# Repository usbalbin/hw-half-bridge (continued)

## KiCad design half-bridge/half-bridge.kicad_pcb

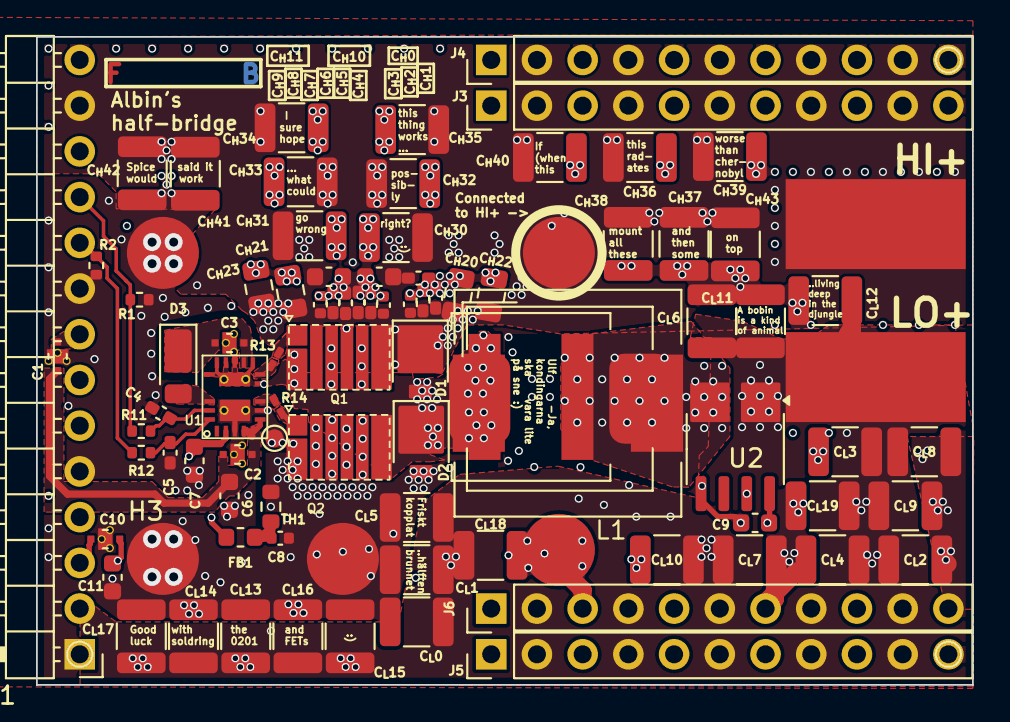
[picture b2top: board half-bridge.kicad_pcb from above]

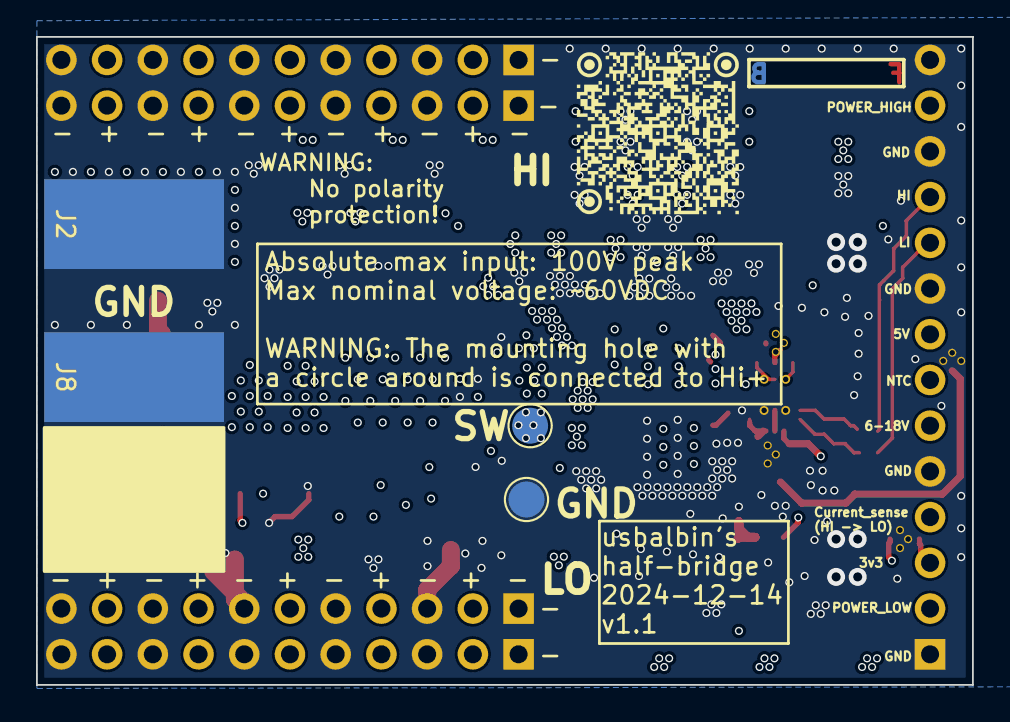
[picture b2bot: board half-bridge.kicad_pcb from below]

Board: 8 copper layers, 52.0 x 36.0 mm, 99 parts (4 on the bottom side), 23 nets.

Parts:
C1, C2, C3, C10: YFF18PW0J474M; C_0603_1608Metric_Feedthrough_W_0.45Vias
C4, C5: ?pF; C_0402_1005Metric_Pad0.74x0.62mm_HandSolder
C6, C7, C11: 10u; C_0603_1608Metric
C8: 100nF; C_0402_1005Metric
C9: 100nF; C_0603_1608Metric
C_{H}0, C_{H}1, C_{H}2, C_{H}5, C_{H}6, C_{H}7, C_{H}8: 100nF; C_0402_1005Metric_Pad0.74x0.62mm_HandSolder
C_{H}3, C_{H}4, C_{H}9: 100nF; C_0402_1005Metric
C_{H}10, C_{H}11: 220nF; C_0603_1608Metric
C_{H}20, C_{H}21, C_{H}22, C_{H}23: 1uF; C_0805_2012Metric
C_{H}30, C_{H}31, C_{H}32, C_{H}33, C_{H}34, C_{H}35, C_{H}36, C_{H}37, C_{H}38, C_{H}39, C_{H}40, C_{H}41, C_{H}42, C_{H}43: 10uF; C_1210_3225Metric
C_{L}0, C_{L}1, C_{L}2, C_{L}3, C_{L}4, C_{L}5, C_{L}6, C_{L}7, C_{L}8, C_{L}9, C_{L}10, C_{L}11, C_{L}12, C_{L}13, C_{L}14, C_{L}15, C_{L}16, C_{L}17, C_{L}18, C_{L}19: 10uF; C_1210_3225Metric
D1, D2: D_Schottky; D_SMP_DO-220AA
D3: DFLS1100; D_PowerDI-123
FB1: FerriteBead; L_0603_1608Metric
FID1, FID2, FID3: Fiducial; TestPoint_Pad_D1.0mm
H1, H2, H3, H4, H5: WE 97730256330; Mounting_Wuerth_WA-SMSI-M1.6_H2.5mm_ThreadDepth1.5mm_NoNPTH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
J1: Angled PinHeader 1x14; PinHeader_1x14_P2.54mm_Horizontal
J2, J7, J8, J9: Solder_Pad; SolderWirePad_1x01_SMD_5x10mm
J3, J4, J5, J6: PinSocket 1x11; PinHeader_1x11_P2.54mm_Vertical
L1: ind=1.76uH esr=9.77m epc=9.28pF; L_Coilcraft_XAL8080-XXX
L4: L_Wuerth_WE-PD-Typ-LS
L5: L_Bourns_SRP1050WA
Q1, Q2: EPC2306; EPC PQFN 3x5 mm
R1, R2: 15k; R_0402_1005Metric
R11, R12: 100R; R_0402_1005Metric
R13, R14: 1R; R_0201_0603Metric_Pad0.64x0.40mm_HandSolder
TH1: 10k; R_0603_1608Metric
TP1, TP2: TestPoint; TestPoint_Pad_D2.0mm
TP3: TestPoint; TestPoint_Pad_D1.0mm
U1: LMG1210; lmg1210
U2: ACS37030; ACS3703x

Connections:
0: C1.2, C2.2, C4.2, C5.2, C6.2, C7.2, C8.2, C9.1, C10.2, C11.2, C_{H}0.2, C_{H}1.2, C_{H}2.2, C_{H}3.2, C_{H}4.2, C_{H}5.2, C_{H}6.2, C_{H}7.2, C_{H}8.2, C_{H}9.2, C_{H}10.2, C_{H}11.2, C_{H}20.2, C_{H}21.2, C_{H}22.2, C_{H}23.2, C_{H}30.2, C_{H}31.2, C_{H}32.2, C_{H}33.2, C_{H}34.2, C_{H}35.2, C_{H}36.2, C_{H}37.2, C_{H}38.2, C_{H}39.2, C_{H}40.2, C_{H}41.2, C_{H}42.2, C_{H}43.2, C_{L}0.2, C_{L}1.2, C_{L}2.2, C_{L}3.2, C_{L}4.2, C_{L}5.2, C_{L}6.2, C_{L}7.2, C_{L}8.2, C_{L}9.2, C_{L}10.2, C_{L}11.2, C_{L}12.2, C_{L}13.2, C_{L}14.2, C_{L}15.2, C_{L}16.2, C_{L}17.2, C_{L}18.2, C_{L}19.2, D2.2 (A), H1.1, H3.1, H4.1, H5.1, J1.1, J1.5, J1.9, J1.12, J1.14, J2.1, J3.1, J3.3, J3.5, J3.7, J3.9, J3.11, J4.1, J4.3, J4.5, J4.7, J4.9, J4.11, J5.1, J5.3, J5.5, J5.7, J5.9, J5.11, J6.1, J6.3, J6.5, J6.7, J6.9, J6.11, J8.1, Q2.2 (S), Q2.4 (S), Q2.6 (S), R1.1, R2.1, TH1.2, TP2.1, TP3.1, U1.3 (Vss), U1.7 (Vss), U1.20 (Vss), U2.3 (GND)
6-18V: C7.1, J1.6, U1.2 (Vin)
+3V3: C9.2, C10.3, C11.1, U2.6 (VDD)
+5V: C1.3, C2.1, C2.3, C6.1, U1.4 (Vdd), U1.5 (DHL), U1.6 (DLH)
/HI: J1.11, R1.2, R11.1
/HO: R13.1, U1.10 (HO)
/I_Shunt: L1.2, L4.2, L5.2, U2.2 (IP-)
/LI: J1.10, R2.2, R12.1
/LO: R14.1, U1.8 (LO)
Current_sense: J1.4, U2.5 (VOUT)
Gate_hi: Q1.1 (G), R13.2
Gate_lo: Q2.1 (G), R14.2
NTC: FB1.1, J1.7
unnamed: C8.1, FB1.2, TH1.1
unnamed: D3.2 (A), U1.17 (BST)
unnamed: C3.1, C3.3, D3.1 (K), U1.12 (HB)
unnamed: C10.1, J1.3
unnamed: C1.1, J1.8
unnamed: C4.1, R11.2, U1.18 (EN/HI)
unnamed: C5.1, R12.2, U1.19 (PWM/LO)
POWER_HIGH: C_{H}0.1, C_{H}1.1, C_{H}2.1, C_{H}3.1, C_{H}4.1, C_{H}5.1, C_{H}6.1, C_{H}7.1, C_{H}8.1, C_{H}9.1, C_{H}10.1, C_{H}11.1, C_{H}20.1, C_{H}21.1, C_{H}22.1, C_{H}23.1, C_{H}30.1, C_{H}31.1, C_{H}32.1, C_{H}33.1, C_{H}34.1, C_{H}35.1, C_{H}36.1, C_{H}37.1, C_{H}38.1, C_{H}39.1, C_{H}40.1, C_{H}41.1, C_{H}42.1, C_{H}43.1, D1.1 (K), H2.1, J1.13, J3.2, J3.4, J3.6, J3.8, J3.10, J4.2, J4.4, J4.6, J4.8, J4.10, J7.1, Q1.3 (D), Q1.5 (D), Q1.7 (D)
POWER_LOW: C_{L}0.1, C_{L}1.1, C_{L}2.1, C_{L}3.1, C_{L}4.1, C_{L}5.1, C_{L}6.1, C_{L}7.1, C_{L}8.1, C_{L}9.1, C_{L}10.1, C_{L}11.1, C_{L}12.1, C_{L}13.1, C_{L}14.1, C_{L}15.1, C_{L}16.1, C_{L}17.1, C_{L}18.1, C_{L}19.1, J1.2, J5.2, J5.4, J5.6, J5.8, J5.10, J6.2, J6.4, J6.6, J6.8, J6.10, J9.1, U2.1 (IP+)
Switch_node: C3.2, D1.2 (A), D2.1 (K), L1.1, L4.1, L5.1, Q1.2 (S), Q1.4 (S), Q1.6 (S), Q2.3 (D), Q2.5 (D), Q2.7 (D), TP1.1, U1.9 (HS), U1.11 (HS), U1.13 (HS), U1.14 (HS), U1.15 (HS), U1.16 (HS), U1.21 (HS)

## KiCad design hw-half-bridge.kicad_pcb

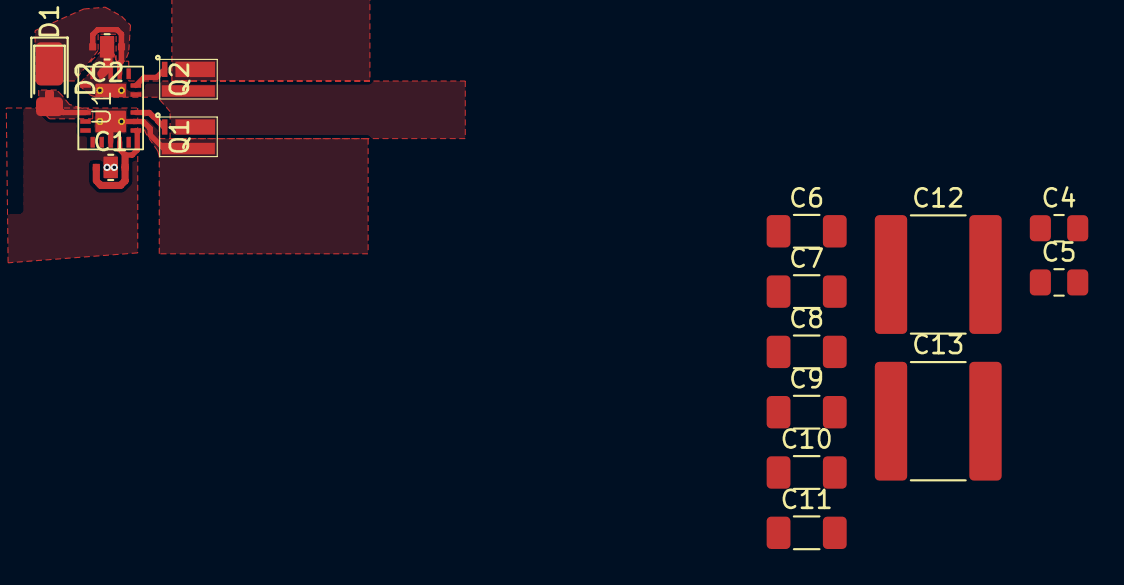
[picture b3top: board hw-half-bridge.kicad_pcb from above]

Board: 2 copper layers, 18 parts (0 on the bottom side), 9 nets.

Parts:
C1, C2: YFF18PW0J474M; C_0603_1608Metric_Feedthrough
C4, C5: C_Small; C_0805_2012Metric_Pad1.18x1.45mm_HandSolder
C6, C7, C8, C9, C10, C11: C; C_1206_3216Metric_Pad1.33x1.80mm_HandSolder
C12, C13: C; C_2225_5664Metric_Pad1.80x6.60mm_HandSolder
D1: BAT46; D_SOD-323F
D2: DFLS1200; D_PowerDI-123
NT1: NetTie-2_SMD_Pad0.5mm
Q1, Q2: GAN7R0-150LBE; FCLGA3(SOT8073-1)
U1: LMG1210; lmg1210

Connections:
5V: C1.1, C1.3, U1.4 (Vdd), U1.6 (DLH)
Earth: C1.2, NT1.1, U1.3 (Vss), U1.20 (Vss)
Gate_hi: Q2.1 (G), U1.10 (HO)
Gate_lo: Q1.1 (G), U1.8 (LO)
unnamed: D1.2 (A), D2.2 (A), U1.17 (BST)
unnamed: C2.1, C2.3, D1.1 (K), D2.1 (K), U1.12 (HB)
unnamed: C2.2, Q1.3 (D), Q2.2 (S), U1.9 (HS), U1.11 (HS), U1.13 (HS), U1.14 (HS), U1.15 (HS), U1.16 (HS), U1.21 (HS)
PGND: C4.2, C5.2, C6.2, C7.2, C8.2, C9.2, C10.2, C11.2, C12.2, C13.2, NT1.2, Q1.2 (S), U1.7 (Vss)
Vbus: C4.1, C5.1, C6.1, C7.1, C8.1, C9.1, C10.1, C11.1, C12.1, C13.1, Q2.3 (D)

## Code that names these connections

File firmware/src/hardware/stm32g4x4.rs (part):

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    delay::SYSTDelayExt,
    gpio::{
        self,
        gpioa::{PA0, PA1, PA2, PA3, PA4, PA5, PA6, PA7},
        gpiob::{PB0, PB11, PB14, PB2},
        gpioc::{PC0, PC1, PC2, PC3, PC4, PC5},
        gpiof::{PF0, PF1},
        GpioExt,
    },
    observable::{Observable, ObservationLock, ObservationToken, Observed},
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            usb_pd: stm32::UCPD1,

            #[allow(dead_code)]
            usb_dm: gpio::gpioa::PA11<gpio::Input<gpio::Floating>>,
            #[allow(dead_code)]
            usb_dp: gpio::gpioa::PA12<gpio::Input<gpio::Floating>>,

            #[allow(dead_code)]
            cc1: gpio::gpiob::PB6<gpio::Input<gpio::Floating>>,
            #[allow(dead_code)]
            cc2: gpio::gpiob::PB4<gpio::Input<gpio::Floating>>,

            #[allow(dead_code)]
            #[cfg(feature = "usb-pd-db")]
            dbcc1: gpio::gpioa::PA9<gpio::Input<gpio::Floating>>,

            #[allow(dead_code)]
            #[cfg(feature = "usb-pd-db")]
            dbcc2: gpio::gpioa::PA10<gpio::Input<gpio::Floating>>,

            frs: gpio::gpioc::PC12<gpio::Input<gpio::Floating>>,

            en_vconn: gpio::gpioc::PC10<gpio::Input<gpio::Floating>>,

            en_cc: gpio::gpioc::PC13<gpio::Input<gpio::Floating>>,

            // Used to select cc-line for usb pd cable orientation
            cc_select: gpio::gpioc::PC14<gpio::Input<gpio::Floating>>,

            // Use to select direction of current measurements 2-5
            cc_dir: gpio::gpioc::PC15<gpio::Input<gpio::Floating>>,
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
        struct Swd {
            #[allow(dead_code)]
            swdio: gpio::gpioa::PA13<gpio::Input<gpio::Floating>>,
            #[allow(dead_code)]
            swc: gpio::gpioa::PA14<gpio::Input<gpio::Floating>>,
        }

        let pa0 = gpioa.pa0;
        let pa1 = gpioa.pa1;
        let pa2 = gpioa.pa2;
        let pa3 = gpioa.pa3;
        let pa4 = gpioa.pa4;
        let pa5 = gpioa.pa5;
        let pa6 = gpioa.pa6;
        let pa7 = gpioa.pa7;
        let pa8 = gpioa.pa8;
        let pa9 = gpioa.pa9;
        let pa10 = gpioa.pa10;
        let pa11 = gpioa.pa11;
        let pa12 = gpioa.pa12;
        let pa13 = gpioa.pa13;
        let pa14 = gpioa.pa14;
        let pa15 = gpioa.pa15;

        let pb0 = gpiob.pb0;
        let pb1 = gpiob.pb1;
        let pb2 = gpiob.pb2;
        let pb3 = gpiob.pb3;
        let pb4 = gpiob.pb4;
        let pb5 = gpiob.pb5;
        let pb6 = gpiob.pb6;
        let pb7 = gpiob.pb7;
        let pb8 = gpiob.pb8;
        let pb9 = gpiob.pb9;
        let pb10 = gpiob.pb10;
        let pb11 = gpiob.pb11;
        let pb12 = gpiob.pb12;
        let pb13 = gpiob.pb13;
        let pb14 = gpiob.pb14;
        let pb15 = gpiob.pb15;

        let pc0 = gpioc.pc0;
        let pc1 = gpioc.pc1;
        let pc2 = gpioc.pc2;
        let pc3 = gpioc.pc3;
        let pc4 = gpioc.pc4;
        let pc5 = gpioc.pc5;
        let pc6 = gpioc.pc6;
        let pc7 = gpioc.pc7;
        let pc8 = gpioc.pc8;
        let pc9 = gpioc.pc9;
        let pc10 = gpioc.pc10;
        let pc11 = gpioc.pc11;
        let pc12 = gpioc.pc12;
        let pc13 = gpioc.pc13;
        let pc14 = gpioc.pc14;
        let pc15 = gpioc.pc15;

        let pd2 = gpiod.pd2;

        let pf0 = gpiof.pf0;
        let pf1 = gpiof.pf1;

        // LO: CC1 and CC2 are connected to PA9 and PA10
        // HI: HI_4, LI_4, HI_5 and LI_5 are connected to PA8,9,10 and PB15
        let cc_hi4_hi5_mux = pd2.into_push_pull_output();

        //let pg10 = gpiog.pg10;comp3_b_fb_d_cc1b_pin
        //let _reset_pin = pg10;
        let _boot_pin = pb8;

        let _swd = Swd {
            swdio: pa13,
            swc: pa14,
        };

        let _usb = FakeUsb {
            usb,
            usb_pd: usb_pd,

            usb_dm: pa11,
            usb_dp: pa12,

            cc1: pb6,
            cc2: pb4,

            #[cfg(feature = "usb-pd-db")]
            dbcc1: pa9,
            #[cfg(feature = "usb-pd-db")]
            dbcc2: pa10,

            frs: pc12,
            en_vconn: pc10,
            en_cc: pc13,

            cc_select: pc14,
            cc_dir: pc15,
        };

        // HRTIMF
        let hi_1 = pc6;
        let li_1 = pc7;

        // HRTIMC
        let hi_2 = pb12;
        let li_2 = pb13;

        // HRTIME
        let hi_3 = pc8;
        let li_3 = pc9;

        // HRTIMD
        #[cfg(feature = "hv4")]
        let li_4 = pb15; // HRTIMD

        #[cfg(feature = "hv4")]
        let hi_4 = pa10; // HRTIMB
                         //let li_b = pa11; // HRTIMB <--- Used by USB_DP

        // HRTIMA
        #[cfg(feature = "hv5")]
        let hi_5 = pa8;
        #[cfg(feature = "hv5")]
        let li_5 = pa9; // Used by dbcc1

        let pwm_led1 = pb5.into_alternate(); // 5v tol
        let pwm_led2 = pb7.into_alternate(); // 5v tol
        let pwm_led3 = pb9.into_alternate(); // 5v tol

        let pwm_led4 = pb10.into_alternate(); // 3.6v max
                                              //let pwm_led5 = pa3.into_alternate(); // 3.6v max
        let pwm_led6_pot3_adc1_in12_adc3_in1 = pb1.into_alternate(); // 3.6v max
        let pwm_led7_adc2_in11 = pc5.into_analog(); // TIM1_CH4N  // 3.6v max
        let pwm_led8_adc2_in12 = pb2.into_alternate(); // 3.6v max

        let (led2_tim4, led3_tim4) = dp.TIM4.pwm((pwm_led2, pwm_led3), 20.kHz(), &mut rcc);
        let (led3_tim3, led6_tim3) = dp.TIM3.pwm(
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        let (led4_tim2/*, led5_tim2*/) = dp.TIM2.pwm((pwm_led4/*, pwm_led5*/), 20.kHz(), &mut rcc);
        let led8_tim5 = dp.TIM5.pwm(pwm_led8_adc2_in12, 20.kHz(), &mut rcc);

        let tx = pb3.into_alternate();
        let rx = pa15.into_alternate();
        let uart = dp
            .USART2
            .usart(
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            )
            .unwrap();

        //let comp1_cc4_pin = pb1.into_analog();
        let (_, [op1_cc4_pin, comp1_b_cc4_pin]) = pa1.into_analog().observe();

        //let comp2_cc5_pin = pa3.into_analog(); // No filter and same DAC as comp4
        let (_, [op12_cc5_pin_b, comp2_cc5_pin_b]) = pa7.into_analog().observe(); // CC5
                                                                                  // comp3_b_fb_d on pc1

        let (_, [op3_cc1_pin, comp4_cc1_pin]) = pb0.into_analog().observe();
        // let comp4_pin_b = pe7; only on LQFP80 and larger

        //let comp5_pin = pc7.into_analog(); // Used by HRTIMF_CH2
        let (_, [op4_cc2_pin, comp6_cc2_pin]) = pb11.into_analog().observe();
        //let comp6_pin_b = pd11; only on LQFP100 and larger

        let (_, [op25_cc3_pin, comp7_cc3_pin]) = pb14.into_analog().observe();

        //let comp7_pin_b = pd14; only on LQFP100 and larger

        let ntc_1 = pc0.into_analog();
        let ntc_2 = pc3.into_analog();
        let ntc_3 = pa2.into_analog();
        let ntc_4 = pf0.into_analog();
        let ntc_5 = pa0.into_analog(); // No filter and same DAC as comp1

        //let op1_comp1_b_pin_fb_a = pa1.into_analog();
        // comp4_op3_pin
        let fb_c = pa6.into_analog();
        //let comp3_b_cc1b_pin = pc1.into_analog();

        let adc12_in8_pot = pc2.into_analog();
        let adc1_in4_pot2_pwm_led5 = pa3.into_analog();
        let fb1_lo_adc2_in17 = pa4.into_analog();
        let fb1_hi_adc2_in13 = pa5.into_analog();
        let fb_d_adc2_in5 = pc4.into_analog();
        let fb_b_adc2_in10 = pf1.into_analog();

        let (mut ctrl, _f, eev_inputs) = dp
            .HRTIM_COMMON
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        let (op1, op2, op3, op4, op5, _op6) = dp.OPAMP.split(&mut rcc);

        #[cfg(feature = "cs-op")]
        let op1 = op1.follower(op1_cc4_pin); // PA1 PA3(comp2) PA7
        #[cfg(feature = "cs-op")]
        let op2 = op2.follower(op12_cc5_pin_b); // PA7 PB0(comp4) PB14(comp7)
        #[cfg(feature = "cs-op")]
        let op3 = op3.follower(op3_cc1_pin); // PA1 PB0(comp4)
        #[cfg(feature = "cs-op")]
        let op4 = op4.follower(op4_cc2_pin);
        #[cfg(feature = "cs-op")]
        let op5 = op5.follower(op25_cc3_pin);
        // PB11(comp6)
        //let op5 = op5.follower(ntc_2_op5, None::<gpio::gpioa::PA8<hal::gpio::Analog>>); // PB14(comp7) PC3
        // let op6 = op6.follower((), None);

        let ad_channels = AdcChannels {
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        hrtime: HRTIM_TIME,
        hrtimf: HRTIM_TIMF,

        hi_1: gpio::gpioc::PC6<gpio::Input<gpio::Floating>>,
        li_1: gpio::gpioc::PC7<gpio::Input<gpio::Floating>>,
        hi_2: gpio::gpiob::PB12<gpio::Input<gpio::Floating>>,
        li_2: gpio::gpiob::PB13<gpio::Input<gpio::Floating>>,
        hi_3: gpio::gpioc::PC8<gpio::Input<gpio::Floating>>,
        li_3: gpio::gpioc::PC9<gpio::Input<gpio::Floating>>,
        #[cfg(feature = "hv4")] li_4: gpio::gpiob::PB15<gpio::Input<gpio::Floating>>,
        #[cfg(feature = "hv4")] hi_4: gpio::gpioa::PA10<gpio::Input<gpio::Floating>>,
        #[cfg(feature = "hv5")] hi_5: gpio::gpioa::PA8<gpio::Input<gpio::Floating>>,
        #[cfg(feature = "hv5")] li_5: gpio::gpioa::PA9<gpio::Input<gpio::Floating>>,
        eevs: &Eevs,
        mut hr_ctrl: HrPwmControl,
    ) -> Timers {
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    fn init(
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
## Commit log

2023-11-12 Redo for kicad 7.0 stable
2023-11-14 More work mainly on layout
2023-11-15 Remove path thing
2023-11-15 Use kicad 7.0
2023-11-17 Update CI
2023-11-17 Some changes
2023-11-17 Add drc rules and fix some errors
2023-11-19 Start adding inductor current sense, adjust some vias and add input filtering
2023-11-19 More work on current sense
2023-11-19 More work on layout
2023-11-19 More work on layout for current signals
2023-11-19 Add footprints for feedthrough cap and 'heatsink'
2023-11-20 More cap
2024-02-27 Some improvements
2024-02-28 One gnd
2024-03-04 More changes, start work on simulating things
2024-03-04 Add spice lib
2024-03-09 Test EPC gan fet
2024-03-10 Sim changes
2024-03-13 More sim changes
2024-03-17 Lots of changes
    * Add smaller fast caps for input decoupling
    * Route current sense
    * Make footprint for more FETs. Still not sure which one to pick...
    * Controller board will be left of pcb stack stack instead of on top - no need for 0ohms to route signals
    * Some sim changes
2024-03-19 Add controller
2024-03-19 Add pin sockets
2024-03-20 Update kibot config for kicad 8
2024-04-01 Try to move closer to what EPC calls 'Optimal layout'
2024-04-02 Further layout improvements
2024-04-03 Clean up overlapping vias and zones
2024-04-04 More changes
2024-04-04 Add lib
2024-04-07 Add heat-spreader
2024-04-10 Add some more small cap
2024-04-13 Add NTC
2024-04-14 Add diodes and make room for larger inductors
2024-04-14 Add current sense resistors
2024-04-14 Footprint - Add R_0508
2024-04-15 Cleanup most DRC errors
2024-04-17 Some improvements to gate loop
2024-04-27 Change paths to 3d models
2024-04-27 Change more paths to 3d models
2024-04-27 Add some step files
2024-04-28 Slightly increase POWER_HIGH area
2024-04-29 Increase POWER_HIGH area further
2024-05-01 Some drc fixes
2024-05-05 Change pinout and add voltage regulators to controller
2024-05-07 Controller - Add labels for pin functions
2024-05-10 Fixup reference designators, more work on controller etc
2024-05-11 WIP - Reduce size and bump to 6 layers
2024-05-13 More work on controller - Add decoupling caps for mcu etc
2024-05-14 Add wifi module
2024-05-19 Cleanup, add more cap etc
2024-05-19 Use custom KiBot config
2024-05-19 Use custom KiBot config - new try
2024-05-19 Use custom KiBot config - newer try
2024-05-19 Use custom KiBot config - newerer try
2024-05-19 Update BOM
2024-05-19 Use custom KiBot config - newererer try
2024-05-19 Use kicad 8
2024-05-19 Use custom KiBot config - newerererer try
2024-05-19 Use custom KiBot config - newererererer try
2024-05-19 Use custom KiBot config - newererererererst try
2024-05-19 Use custom KiBot config - Add KiCost config
2024-05-23 Revert to quick start config for kibot
2024-05-26 Add plugin for placing vias
2024-05-27 Improve plugin for placing vias
2024-06-01 Increase via size
2024-06-01 Update via script
2024-06-01 Fix more ERC and DRC errors and warnings
2024-06-01 Improve via placement
2024-06-01 Change some remaining vias to 0.45/0.3mm
2024-06-01 Attempt to slightly improve isolation distance
2024-06-01 Larger via size in lmg1210 footprint
2024-06-01 Add feedthrough cap with larger vias
2024-06-02 Dont use custom 3D model for MLCC
2024-06-02 Update workflow
2024-06-02 Update workflow for kicost
2024-06-02 Fix kicost
2024-06-02 kicost - use SEK as currency
2024-06-03 Add caching, try fixing running twice on push to pr
2024-06-04 Try to fix caching
2024-06-04 Try to fix kicost
2024-06-09 Try use custom kibot config, again...
2024-06-09 try again
2024-06-22 Add extra OP, close hole in planes under switch node
2024-06-22 Add layers for a total of 8 copper layers. Add comments in silkscreen and some test points
2024-06-23 Some more adjustments
2024-06-23 Even more adjustments
2024-09-01 Controller - More changes
2024-09-01 Break out ESP to sub circuit
2024-09-01 Add hierarchial sheets
2024-09-01 Controller - Some smaller changes, add 3d models etc
2024-09-01 Firmware - Update some WIP work on regulator etc.
2024-09-01 FW - stm32g4 - Add code
2024-09-01 Controller move DC/DC to between HB4 and HB5
2024-09-01 Add .gitignore
2024-09-01 Remove USB CC protections
2024-09-01 Probably nothing
2024-09-01 Controller - Try to simplify
2024-09-01 Controller - Lots of changes
2024-09-01 Controller - Route extra usb's CC-pins and some other pins to pin header
2024-09-01 More work on controller
2024-09-01 Controller - More work mainly on layout
2024-09-01 Update some pin names
2024-09-01 Controller - some more changes
2024-09-01 Firmware - Add ci
2024-09-01 Controller - Some more pin related changes
2024-09-01 Controller - All currents can now be read by ADCs
2024-09-01 Controller and firwmare most pins in sync
2024-09-01 More work on pins (Controller and firwmare)
2024-09-05 Controller - Route mcu pins
2024-09-05 Controller - Route more mcu pins
2024-09-07 Controller - Even more pins
2024-09-08 Controller - Start work on vbus connection, improve rgb-led placement
2024-09-12 Controller - Setup clearance, place rgb led resistors, some more routing and step down current sense
2024-09-16 Half Bridge - Change current sensor
2024-09-18 Controller - Change current sensor
2024-09-22 Controller - More routing
2024-09-22 Some work on firmware
2024-09-26 Controller - Expand to 100x40mm
2024-09-26 Add current sensor
2024-09-29 Add step for inductance
2024-09-29 Controller - Some changes
2024-10-07 Add new led
2024-10-13 Add new leds
2024-10-20 Controller - Expand to 100x50mm to allow VBUS to go around
2024-10-21 Controller - Lots of cleanup
2024-10-27 Controller - Add custom dcr rules
2024-10-27 Controller - NTCs done
2024-10-28 Controller - Most things routed
2024-10-29 Controller - Add rotary encoder
2024-10-31 HB - Fix DRC errors
2024-10-31 Controller - More work around rotary encoder and move protection diodes
2024-12-02 Controller - Fix all DRC errors and some warnings
2024-12-15 Controller - Cleanup and improve silkscreen
2024-12-15 Half-Bridge - Fix DRC errors
2024-12-27 FW -Compiles
2024-12-27 FW - Refactor
2024-12-27 FW - More refactor
2025-01-06 half-bridge - Update BOM
2025-01-06 controller - Update BOM - WIP
2025-01-06 controller - Update BOM
2025-01-06 Trick KiCost to not lookup buggy WS2812B price
2025-01-06 Sync PCBs with scematics
2025-01-12 HB - Some BOM cleanup
2025-04-27 bork
2025-05-17 Fix ARTIKELKOD in ibom
2025-05-17 Add mounting holes to BOM
2025-05-17 Add part-num in ibom
2025-05-26 Work on control, update pac, more...
2025-05-26 bump stm32-hrtim
2025-06-01 Calculate control parameters
2025-06-01 Take some math functions from rust-lang/libm
2025-06-04 Take some more math functions from rust-lang/libm and use some complex math
2025-06-06 Math still not working...
2025-07-06 bin minimal runs
2025-07-07 More work
2025-07-08 Temp and current
2025-07-10 Btn working
2025-07-12 Add heatspreader
2025-07-27 Stuff
2025-07-31 Use probe-plotter
2025-08-04 Add plotting using probe-plotter
2025-08-04 Fix hi/lo mixup, add current limit
2025-08-13 Fix the math
    The math now gives the same result for the example in 'Hallworth, M. and Shirsavar, A. (2012) Microcontroller-based
    peak current mode control using digital slope compensation'
2025-08-13 Constify math again
2025-08-13 Fix some warnings
2025-08-14 Clean up math, work on control
2025-08-14 Add runtime metric
2025-08-14 More work on control
2025-09-13 Various changes
2026-02-20 Fix the math with lots of help from Claude
2026-02-21 Add support for boost and buck-boost with with lots of help from Claude
2026-03-17 Add peak current mode controlled buck converter with probe-plotter support and dynamic slope compensation - Works ok:ish
2026-03-24 Lots of changes
    * Use actual component values control math
    * Lots of fixes for slope compensation, blanking etc
